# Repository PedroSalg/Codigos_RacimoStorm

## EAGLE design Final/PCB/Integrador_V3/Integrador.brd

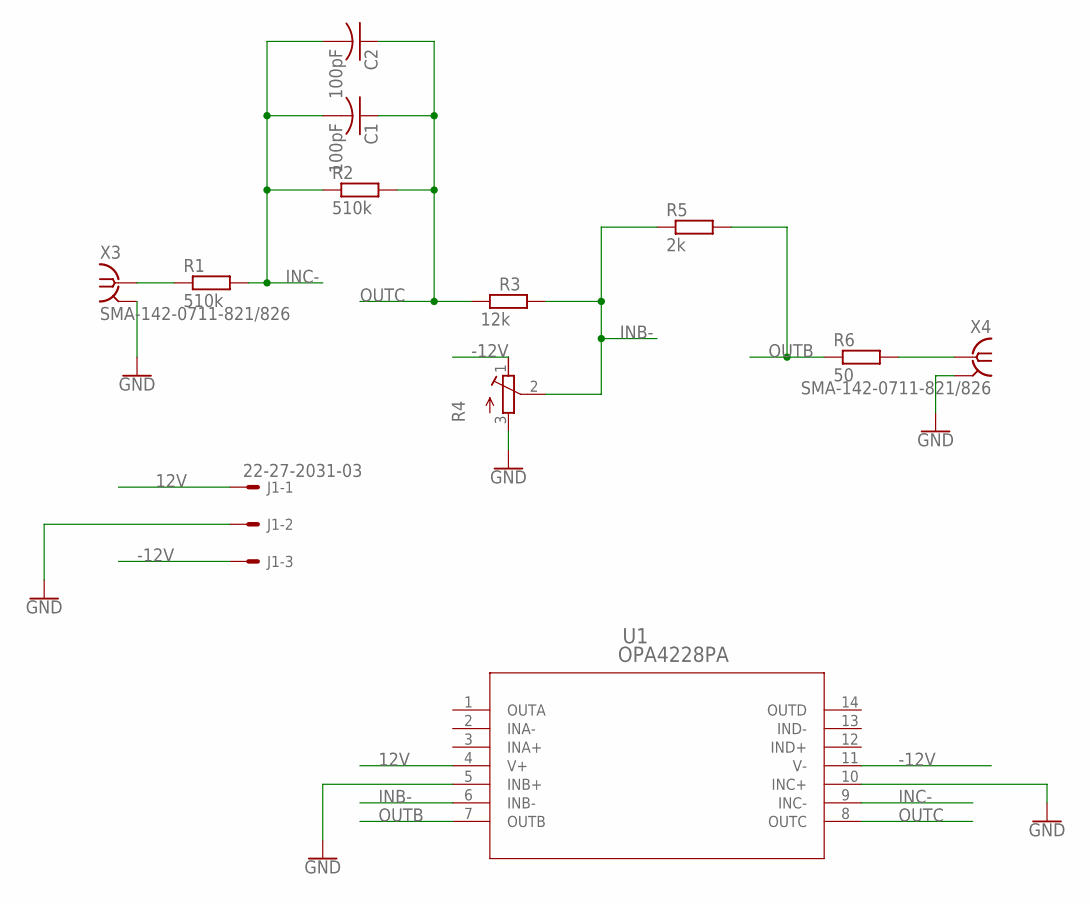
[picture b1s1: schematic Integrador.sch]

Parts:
C1, C2: 100pF; C025-030X050
J1: 22-27-2031-03; 6410-03
R1, R2: 510k; 0207/10
R3: 12k; 0207/10
R4: R-TRIMM3006P; RTRIM3006P
R5: 2k; 0207/10
R6: 50; 0207/10
U1: OPA4228PA; N14
X3, X4: SMA-142-0711-821/826; J502-ND-142-0711-821/826

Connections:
12V: J1.1, U1.4 (V+)
-12V: J1.3, R4.1 (E), U1.11 (V-)
GND: J1.2, R4.3 (A), U1.5 (INB+), U1.10 (INC+), X3.G@1 (2), X3.G@2 (2), X3.G@3 (2), X3.G@4 (2), X4.G@1 (2), X4.G@2 (2), X4.G@3 (2), X4.G@4 (2)
INB-: R3.2, R4.2 (S), R5.1, U1.6 (INB-)
INC-: C1.2, C2.2, R1.2, R2.1, U1.9 (INC-)
unnamed: R1.1, X3.1
unnamed: R6.2, X4.1
OUTB: R5.2, R6.1, U1.7 (OUTB)
OUTC: C1.1, C2.1, R2.2, R3.1, U1.8 (OUTC)

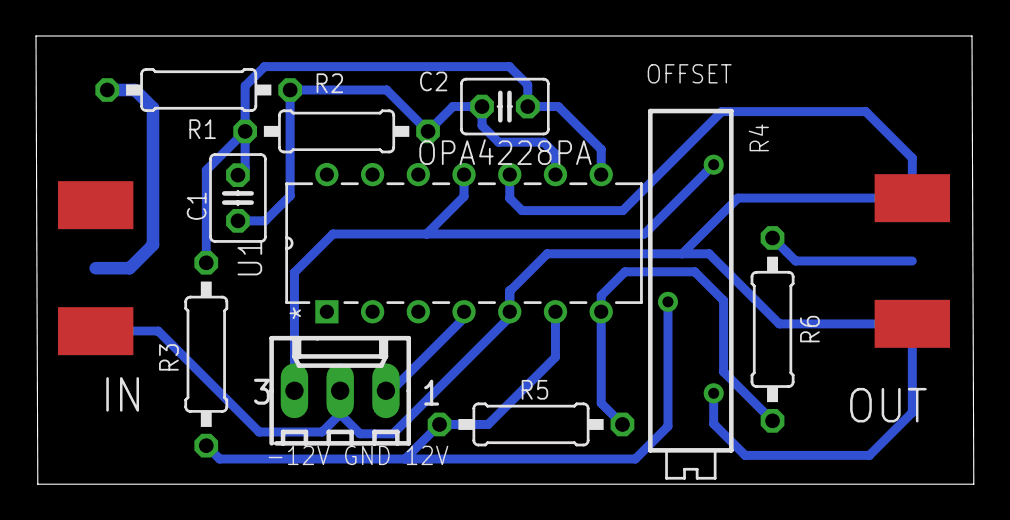
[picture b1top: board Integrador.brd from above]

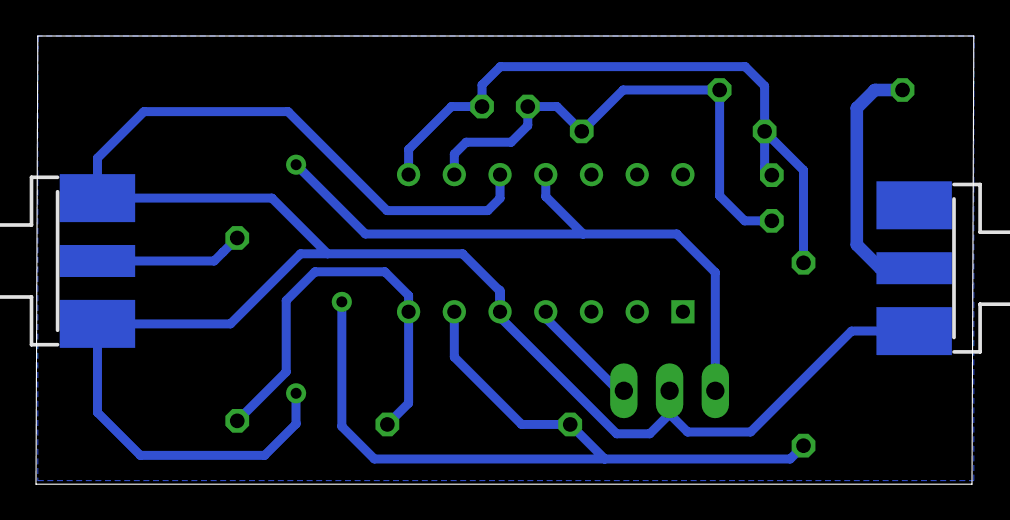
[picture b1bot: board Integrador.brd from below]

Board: 2 copper layers, 52.1 x 24.9 mm, 12 parts (2 on the bottom side), 9 nets.

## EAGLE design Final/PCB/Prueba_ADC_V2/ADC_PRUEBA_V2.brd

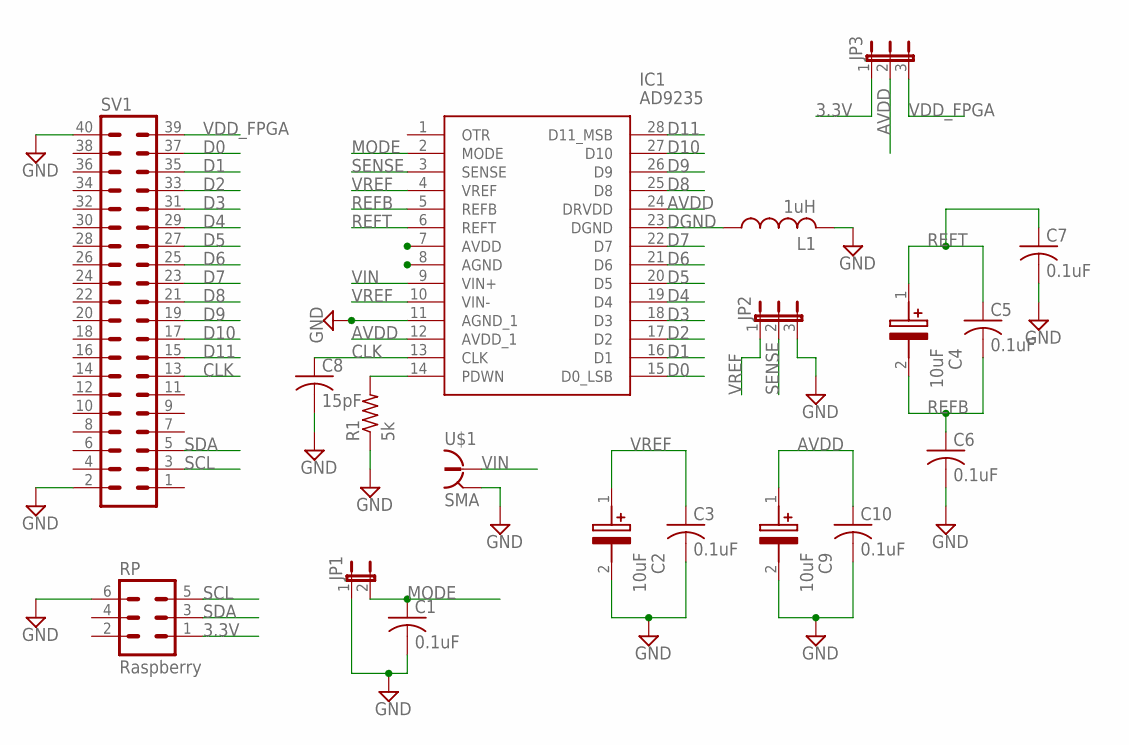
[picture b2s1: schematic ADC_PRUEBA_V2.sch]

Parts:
C1, C3, C5, C6, C7, C10: 0.1uF; C0805K
C2, C4, C9: 10uF; CAPPM6032X280N
C8: 15pF; C0805K
IC1: AD9235; SOP65P638X110-28N
JP1: JP1E; JP1
JP2, JP3: JP2E; JP2
L1: 1uH; L2012C
R1: 5k; R0805
RP: Raspberry; MA03-2
SV1: MA20-2
U$1: SMA

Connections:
3.3V: JP3.1, RP.1
AVDD: C9.1 (+), C10.1, IC1.12 (AVDD_1), IC1.24 (DRVDD), JP3.2
CLK: C8.1, IC1.13 (CLK), SV1.13
D0: IC1.15 (D0_LSB), SV1.37
D1: IC1.16 (D1), SV1.35
D2: IC1.17 (D2), SV1.33
D3: IC1.18 (D3), SV1.31
D4: IC1.19 (D4), SV1.29
D5: IC1.20 (D5), SV1.27
D6: IC1.21 (D6), SV1.25
D7: IC1.22 (D7), SV1.23
D8: IC1.25 (D8), SV1.21
D9: IC1.26 (D9), SV1.19
D10: IC1.27 (D10), SV1.17
D11: IC1.28 (D11_MSB), SV1.15
DGND: IC1.23 (DGND), L1.1
GND: C1.2, C2.2 (-), C3.2, C6.2, C7.2, C8.2, C9.2 (-), C10.2, IC1.11 (AGND_1), JP1.1, JP2.3, L1.2, R1.1, RP.6, SV1.2, SV1.40, U$1.GND, U$1.P$2 (GND), U$1.P$3 (GND), U$1.P$4 (GND)
MODE: C1.1, IC1.2 (MODE), JP1.2
unnamed: IC1.14 (PDWN), R1.2
REFB: C4.2 (-), C5.2, C6.1, IC1.5 (REFB)
REFT: C4.1 (+), C5.1, C7.1, IC1.6 (REFT)
SCL: RP.5, SV1.3
SDA: RP.3, SV1.5
SENSE: IC1.3 (SENSE), JP2.2
VDD_FPGA: JP3.3, SV1.39
VIN: IC1.9 (VIN+), U$1.IN
VREF: C2.1 (+), C3.1, IC1.4 (VREF), IC1.10 (VIN-), JP2.1

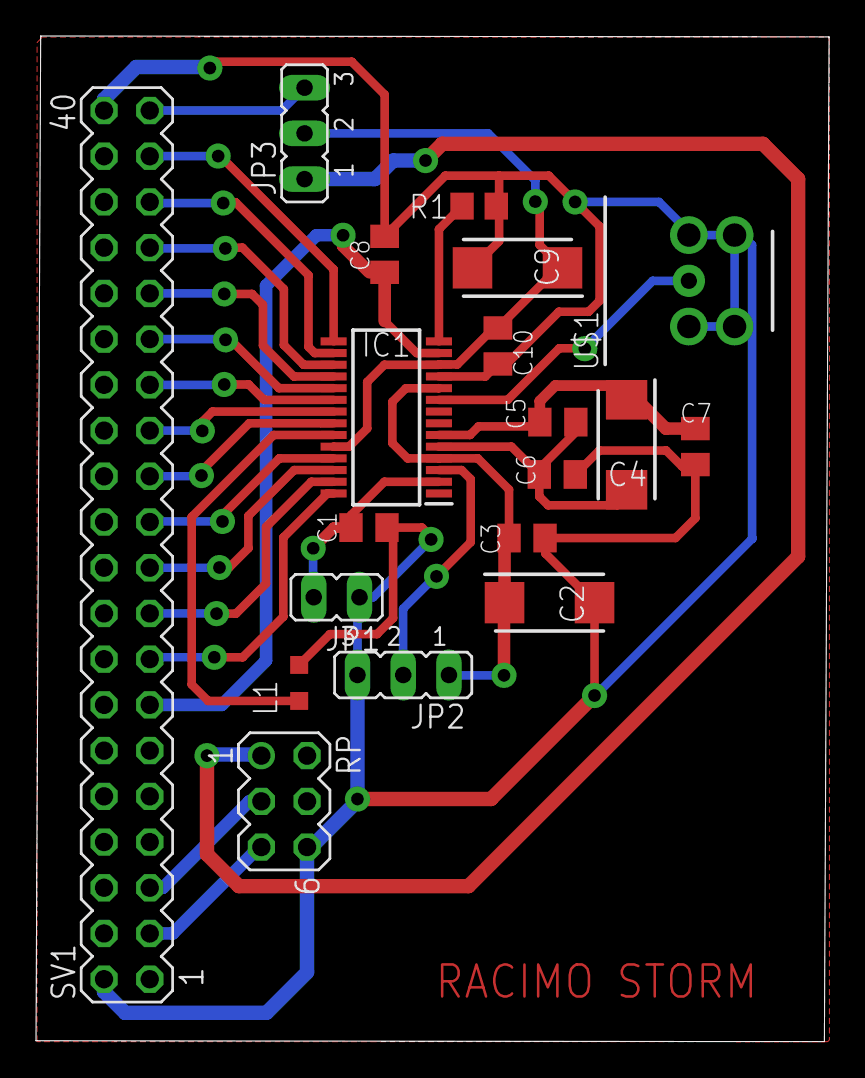
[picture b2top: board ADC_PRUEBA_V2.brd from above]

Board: 2 copper layers, 44.1 x 55.9 mm, 19 parts (0 on the bottom side), 27 nets.

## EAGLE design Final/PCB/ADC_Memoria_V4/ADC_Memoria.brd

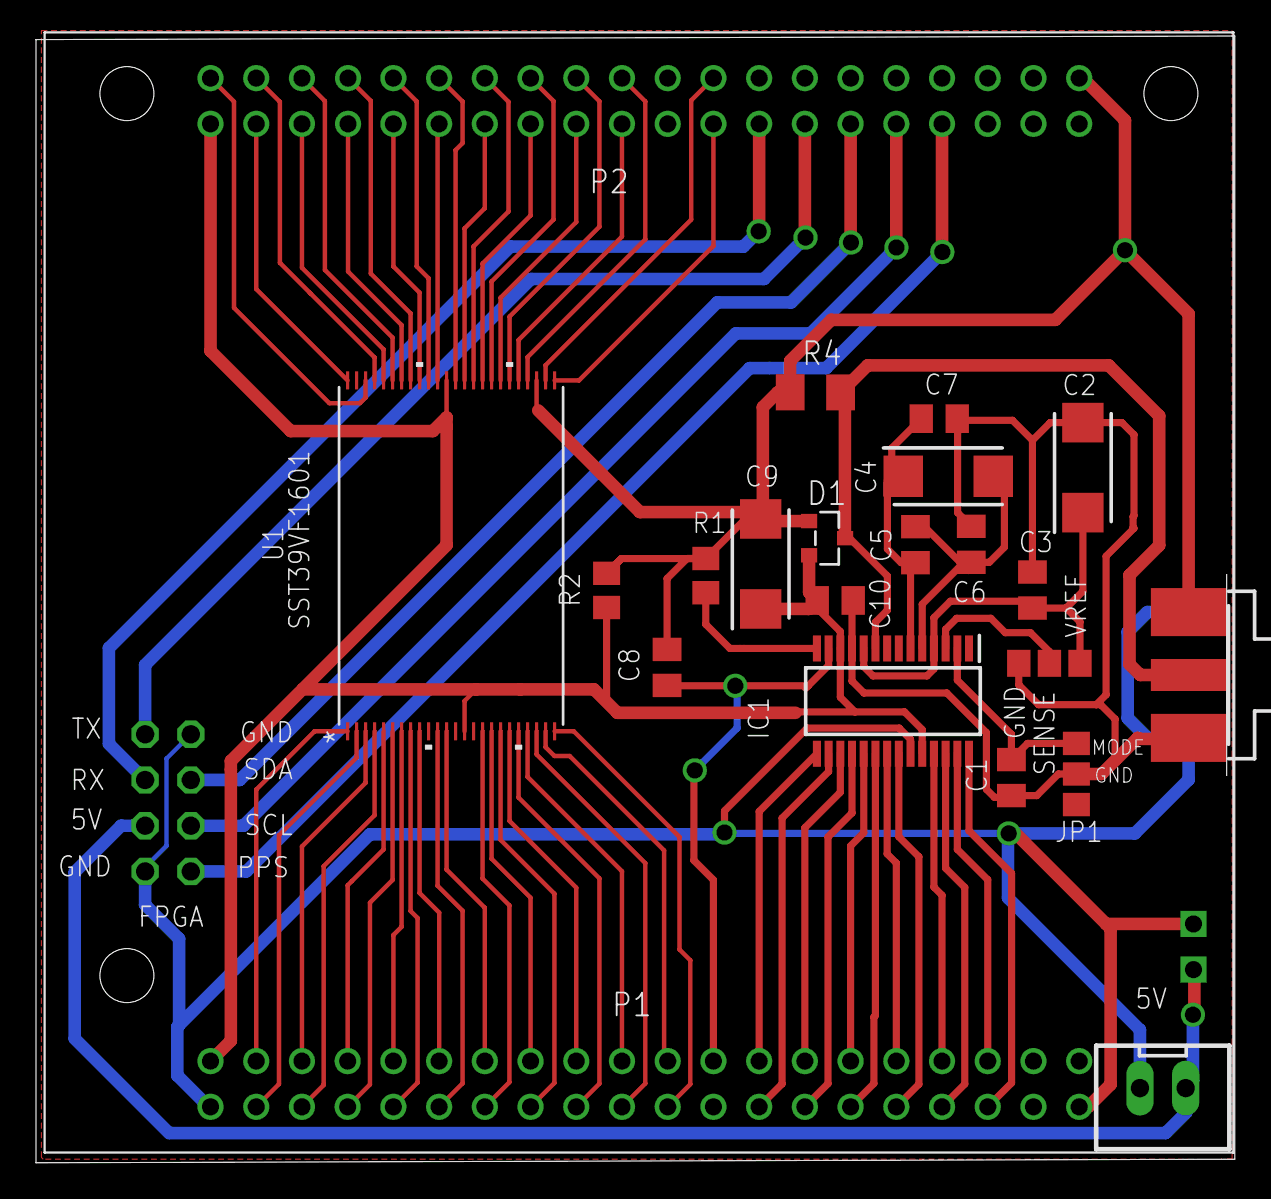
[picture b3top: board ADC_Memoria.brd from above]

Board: 2 copper layers, 66.6 x 62.6 mm, 22 parts (1 on the bottom side), 68 nets.

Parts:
C1, C3, C5, C6, C7, C10: 0.1uF; C0805K
C2, C4, C9: 10uF; CAPPM6032X280N
C8: 15pF; C0805K
D1: PIN_DIODE_287T
GND-SEN-VREF: JP2; A0R-JMP
IC1: AD9235; SOP65P638X110-28N
JP1: GND MODE; A0R-JMP
R1: 5k; R0805
R2: 10k; R0805
R4: 50; M1206
SMA: SIGNAL; J502-ND-142-0711-821/826
U1: SST39VF1601; TSOP48_EKE_SST-L
U$1: SPARTAN_NO_HOLES
U$2: CAPA1
V_EXT: V_Ext; JST-XH-02-PACKAGE-LONG-PAD

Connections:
5V: U$1.5V_E, U$2.5V, V_EXT.1
A0: U1.25, U$1.P2_18
A1: U1.24, U$1.P1_20
A2: U1.23, U$1.P1_19
A3: U1.22, U$1.P1_22
A4: U1.21, U$1.P1_21
A5: U1.20, U$1.P1_24
A6: U1.19, U$1.P1_23
A7: U1.18, U$1.P1_26
A8: U1.8, U$1.P1_32
A9: U1.7, U$1.P1_31
A10: U1.6, U$1.P1_34
A11: U1.5, U$1.P1_33
A12: U1.4, U$1.P1_36
A13: U1.3, U$1.P1_35
A14: U1.2, U$1.P1_38
A15: U1.1, U$1.P1_37
A16: U1.48, U$1.P2_38
A17: U1.17, U$1.P1_25
A18: U1.16, U$1.P1_28
A19: U1.9, U$1.P1_29
AVDD: C9.1, C10.1, D1.T, IC1.12, IC1.24, R2.1, U1.14, U1.37, U$1.P1_VCC1, U$1.P2_VCC1
CE: U1.26, U$1.P2_17
CLK: C8.1, IC1.13, U$1.P1_17
D0: IC1.15, U$1.P1_15
D1: IC1.16, U$1.P1_16
D2: IC1.17, U$1.P1_13
D3: IC1.18, U$1.P1_14
D4: IC1.19, U$1.P1_11
D5: IC1.20, U$1.P1_12
D6: IC1.21, U$1.P1_09
D7: IC1.22, U$1.P1_10
D8: IC1.25, U$1.P1_07
D9: IC1.26, U$1.P1_08
D10: IC1.27, U$1.P1_05
D11: IC1.28, U$1.P1_06
DQ0: U1.29, U$1.P2_22
DQ1: U1.31, U$1.P2_24
DQ2: U1.33, U$1.P2_26
DQ3: U1.35, U$1.P2_28
DQ4: U1.38, U$1.P2_30
DQ5: U1.40, U$1.P2_32
DQ6: U1.42, U$1.P2_34
DQ7: U1.44, U$1.P2_36
DQ8: U1.30, U$1.P2_23
DQ9: U1.32, U$1.P2_25
DQ10: U1.34, U$1.P2_27
DQ11: U1.36, U$1.P2_29
DQ12: U1.39, U$1.P2_31
DQ13: U1.41, U$1.P2_33
DQ14: U1.43, U$1.P2_35
DQ15: U1.45, U$1.P2_37
GND: C1.2, C2.2, C3.2, C6.2, C7.2, C8.2, C9.2, C10.2, D1.B, GND-SEN-VREF.1, IC1.11, IC1.23, JP1.2, R1.1, R2.2, R4.1, SMA.G@1, SMA.G@2, SMA.G@3, SMA.G@4, U1.27, U1.46, U$1.GND_E, U$1.P1_GND, U$1.P1_GND1, U$1.P2_GND, U$1.P2_GND1, U$2.GND, U$2.GND2, V_EXT.2
MODE: C1.1, IC1.2, JP1.1
unnamed: IC1.14, R1.2
OE: U1.28, U$1.P2_21
PPS: U$1.P2_08, U$2.PPS
REFB: C4.2, C5.2, C6.1, IC1.5
REFT: C4.1, C5.1, C7.1, IC1.6
RST: U1.12, U$1.P1_27
RX: U$1.P2_16, U$2.RX2PI
SCL: U$1.P2_10, U$2.SCL
SDA: U$1.P2_12, U$2.SDA
SENSE: GND-SEN-VREF.2, IC1.3
TX: U$1.P2_14, U$2.TX2PI
VIN: D1.O, IC1.9, R4.2, SMA.1
VREF: C2.1, C3.1, GND-SEN-VREF.3, IC1.4, IC1.10
WE: U1.11, U$1.P1_30

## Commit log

2020-03-02 Codigos usados hasta 1 Marzo 2020
2020-03-03 Prueba de ADC en tarjeta version 2 - 2 de Marzo
2020-03-07 Códigos y datos para obtener el diagrama de bode del integrador en su version V3
2020-04-05 Escritura_Lectura_Borrado con pulsadores. Primeras correciones al modulo de escritura
2020-04-05 Escritura_Lectura_Borrado con pulsadores. Con correciones sin archivo UCF
2020-04-05 Escritura_Lectura_Borrado con pulsadores. Con correciones y archivo UCF; Listo para implementar en FPGA
2020-04-07 Escritura y Lectura en todas las direcciones de memoria. No funciona la lecuta, se queda pegado
2020-04-13 Codigo basico de lectura de un boton con GPIOs de Raspberry Pi
2020-04-13 Condigo de comunicacion entre raspberry y FPGA
2020-04-13 Blink de un LED con los GPIOs de la RAspberry
2020-04-13 Lectura datos I2C mandados desde la FPGA, no hay contol en la velocidad de transmision
2020-04-13 Codigo de lectura de un botos con lo GPIOs de la Raspbery y al tiempo encendido de un LED
2020-04-13 Codigo de primeras pruebas de escritura manual de un GPIO de Raspberry
2020-04-22 Lecutura de datos usando I2C desde la FPGA hacia la RP. Datos de la memoria
2020-04-22 Transmision de datos de la memoria en un archivo de texto en la Raspberry
2020-04-23 Comunicacion entre RP y FPGA sin protocolo de inicio
2020-04-23 Primera Version del codigo de comunicacion entre la FPGA y RP, no funcional
2020-04-23 Prueba de cdeteccion de eventos con Switch y Led
2020-04-23 Blink de led con librerio GPIO
2020-04-24 Adquisicion con interrupciones. No funcional
2020-04-24 Condigo contador de eventos
2020-04-25 Comunicacion entre PFGA y Raspberry. Semi funcional
2020-04-25 Version funcional del codigo de adquision de campo electrico rapido
2020-04-25 prueba
2020-04-25 Actualización
2020-04-25 Actualizacio funcional de comunicacion de entre FPGA y Raspberry, 2kbs
2020-04-30 Primera version de codigo FPGA y RP
2020-04-30 Modulos de escritura, lectua, borrado
2020-05-03 Primeras datos obtenidos del ADC con 3 diferentes tensiones
2020-05-03 Graficas de los primeros resultados de ADC
2020-05-03 Version 1 del codigo de adquisicion del campo electrico rapido para la estacion RacimoStorm
2020-05-03 Primera version funcional del codigo de campo rapido para RacimoStorm
2020-05-06 Codigo de adquisicion de campo electrico rapido. Funional para 100k muestras
2020-05-06 Datos para presentacion Halley Miercoles 6 de mayo
2020-05-06 Codigo FPGA RACIMO Storm. Funcional, detecta pulso, lo envia y limpia la memora en espera de un nuevo evento. 100k muestras
2020-05-09 Pulsos registrados en los cuales se ve la falta datos antes de ocurrir el evento, razon por la cual se implementa el registro de 100 muestras antes del evento
2020-05-09 Graficas de presentacion Halley 6 de Mayo
2020-05-09 Actualizacion del codigo de la FPGA
2020-05-09 Analisis de datos de la falencia de datos antes de la detección del evento
2020-05-09 Registro serie Salida serie
2020-05-09 Archivo UCF para la FGPA
2020-05-12 Codigo GPS actulizado
2020-05-12 Transforma a valores de campo
2020-05-12 Nuevo codigo GPS
2020-05-13 Ultima actualizacion codigo adquisicion
2020-05-13 Ultima actualizacion libreria gps adquisicion
2020-05-14 Datos obtenidos de prueba con diferentes pulsos generados por Arduino Mega para ver el minimo ancho de deteccion de evento
2020-05-14 Actualización de archivos de texto plano que se crean
2020-05-14 Codigo de deteccion de evento para ver si logra ver el pulso PPS del GPS
2020-05-14 Código de arduino para general pulso cuadrado de ancho variable para pruebas de deteccion
2020-05-14 Archivos restantes
2020-05-14 Pulsos con microsegundos de ancho
2020-05-14 Pulso_Simulado
2020-05-14 Codigos de arduino para probar puslos emulando senal de antena rapida
2020-05-16 Registro de entrada Serie salida serie
2020-05-25 Actualizacion funcional con implementacion de memoria temporal
2020-06-04 Codigo de adquisicion de campo rapido funcional
2020-06-11 Señal sinusoidal para prueba del trigger 1
2020-06-12 Codigo final de adquisicion de campo rapido funcional
2020-06-12 Codigo python para extraer informacion de la ultima linea de codifo de los datos de la estacion
2020-06-13 Datos y analisis del contador clk del gps
2020-06-16 Ultima version del codigo de adquisición
2020-08-05 Versión final del proyecto

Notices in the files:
parts and their libraries:
SparkFun-PowerSymbols: Licensing: Creative Commons ShareAlike 4.0 International - https://creativecommons.org/licenses/by-sa/4.0
